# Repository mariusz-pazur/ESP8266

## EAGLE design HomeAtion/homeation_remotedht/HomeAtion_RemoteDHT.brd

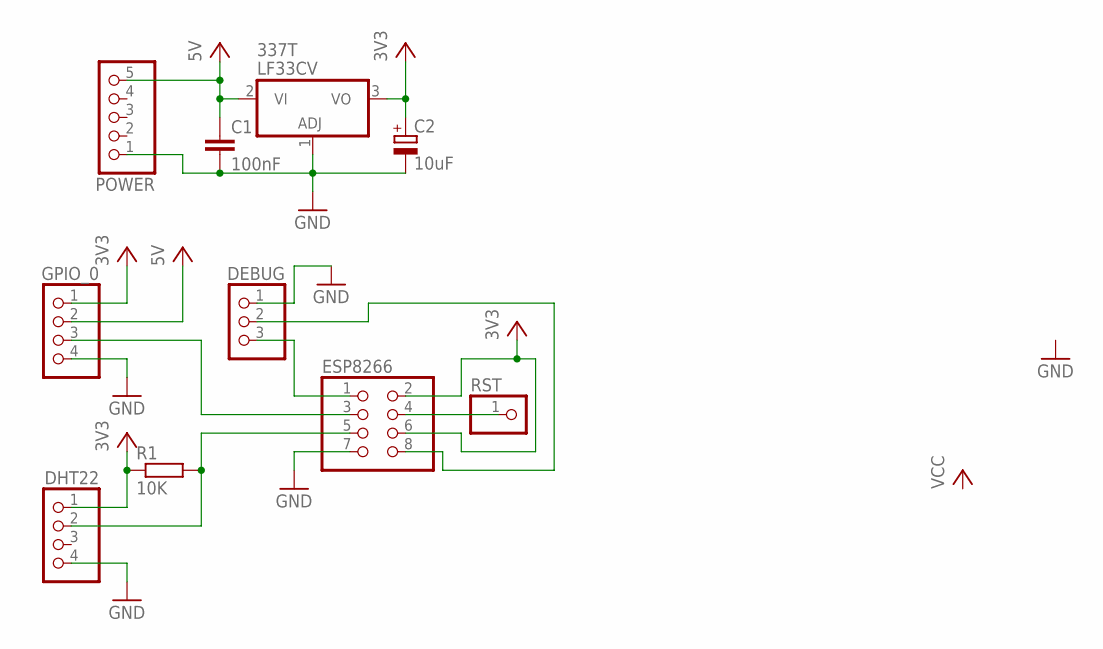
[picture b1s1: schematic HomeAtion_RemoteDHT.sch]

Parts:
C1: 100nF; C2.5-5
C2: 10uF; B45181A
DEBUG: PINHD-1X3; 1X03
DHT22: PINHD-1X4; 1X04
ESP8266: PINHD-2X4; 2X04
GPIO_0: PINHD-1X4; 1X04
LF33CV: 337T; TO220H
POWER: PINHD-1X5; 1X05
R1: 10K; 0204/7
RST: PINHD-1X1; 1X01

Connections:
GND: C1.2, C2.-, DEBUG.1, DHT22.4, ESP8266.7, GPIO_0.4, LF33CV.1 (ADJ), POWER.1
unnamed: DEBUG.3, ESP8266.1
unnamed: DEBUG.2, ESP8266.8
unnamed: ESP8266.4, RST.1
unnamed: DHT22.2, ESP8266.5, R1.2
unnamed: ESP8266.3, GPIO_0.3
VCC: C1.1, C2.+, DHT22.1, ESP8266.2, ESP8266.6, GPIO_0.1, GPIO_0.2, LF33CV.2 (VI), LF33CV.3 (VO), POWER.5, R1.1

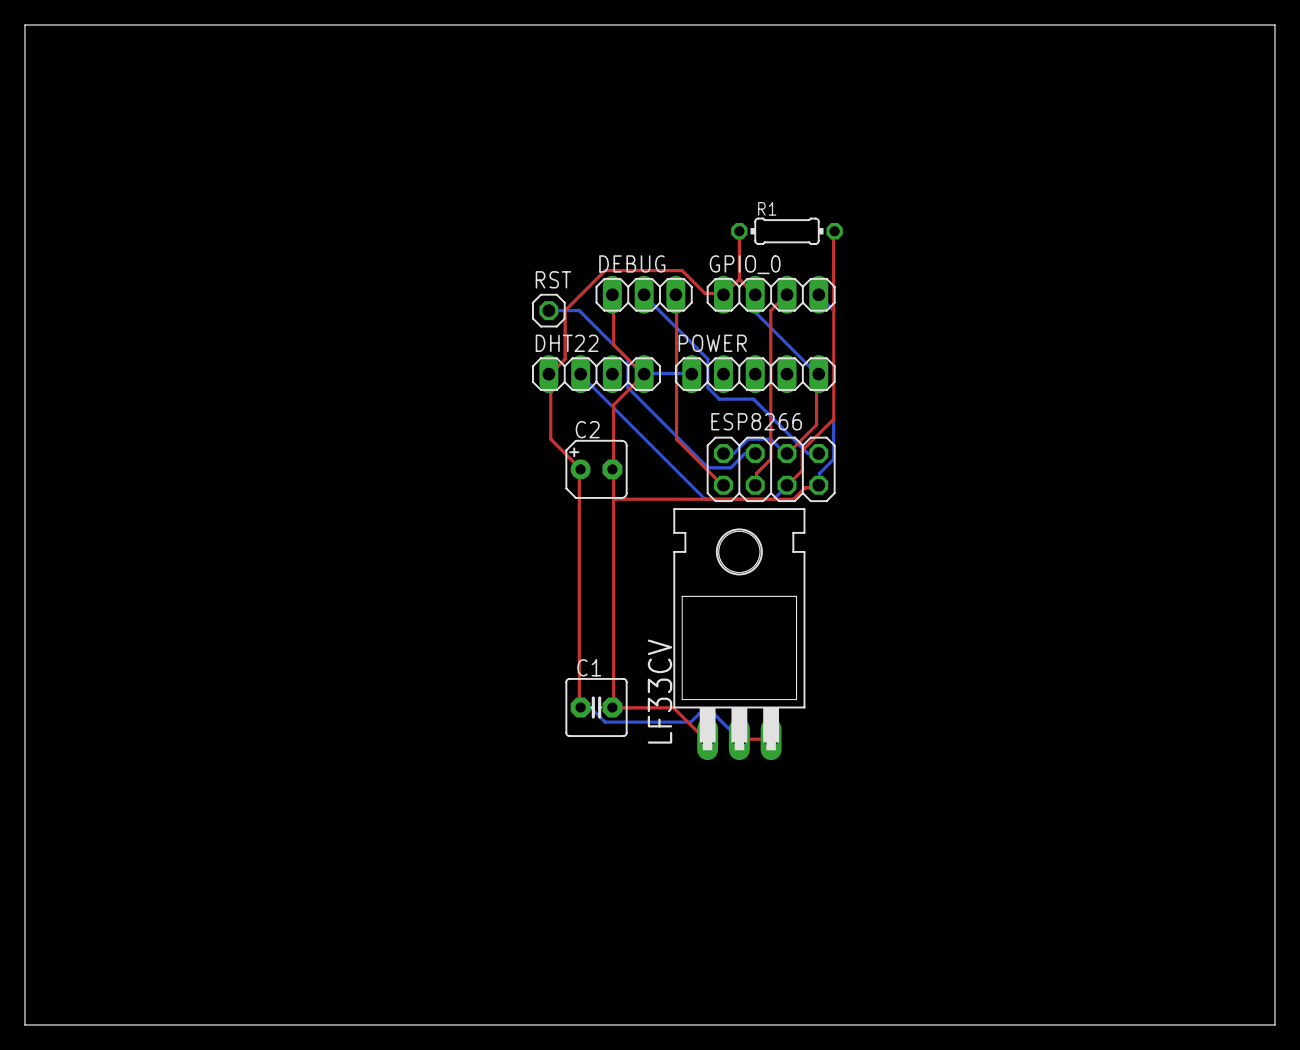
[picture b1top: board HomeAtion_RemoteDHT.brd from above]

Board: 2 copper layers, 100.0 x 80.0 mm, 10 parts (0 on the bottom side), 7 nets.

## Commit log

2016-01-15 :circus_tent: Added .gitattributes
2016-01-15 Test ESP8266 i DHT22
2016-02-01 HomeAtion-RemoteDHT na ESP8266
    Plus wykorzystanie biblioteki WiFiManager
2016-02-06 HomeAtion_RemoteDHT w Visual Micro + design programatora do ESP
2016-02-06 gitignore
2016-02-06 HomeAtion_RemoteDHT - projekt płytki
2016-02-13 HomeAtion_RemoteDHT - wysyłanie do Thingspeak
2016-02-15 HomeAtion_RemoteDHT_ClientOnly
2016-02-16 HomeAtion_RemoteDHT - schemat i board w Eagle
2016-02-24 HomeAtion_RemoteDHT - test 4 czujników
2016-02-24 HomeAtion-RemoteDHTLedBuzz
2016-03-17 HomeAtionRemoteDhtLedBuzz - obsługa LED, brak pamięci na SPI
2016-03-17 HomeAtionRemoteDhtLedBuzz - obsługa Domoticz
